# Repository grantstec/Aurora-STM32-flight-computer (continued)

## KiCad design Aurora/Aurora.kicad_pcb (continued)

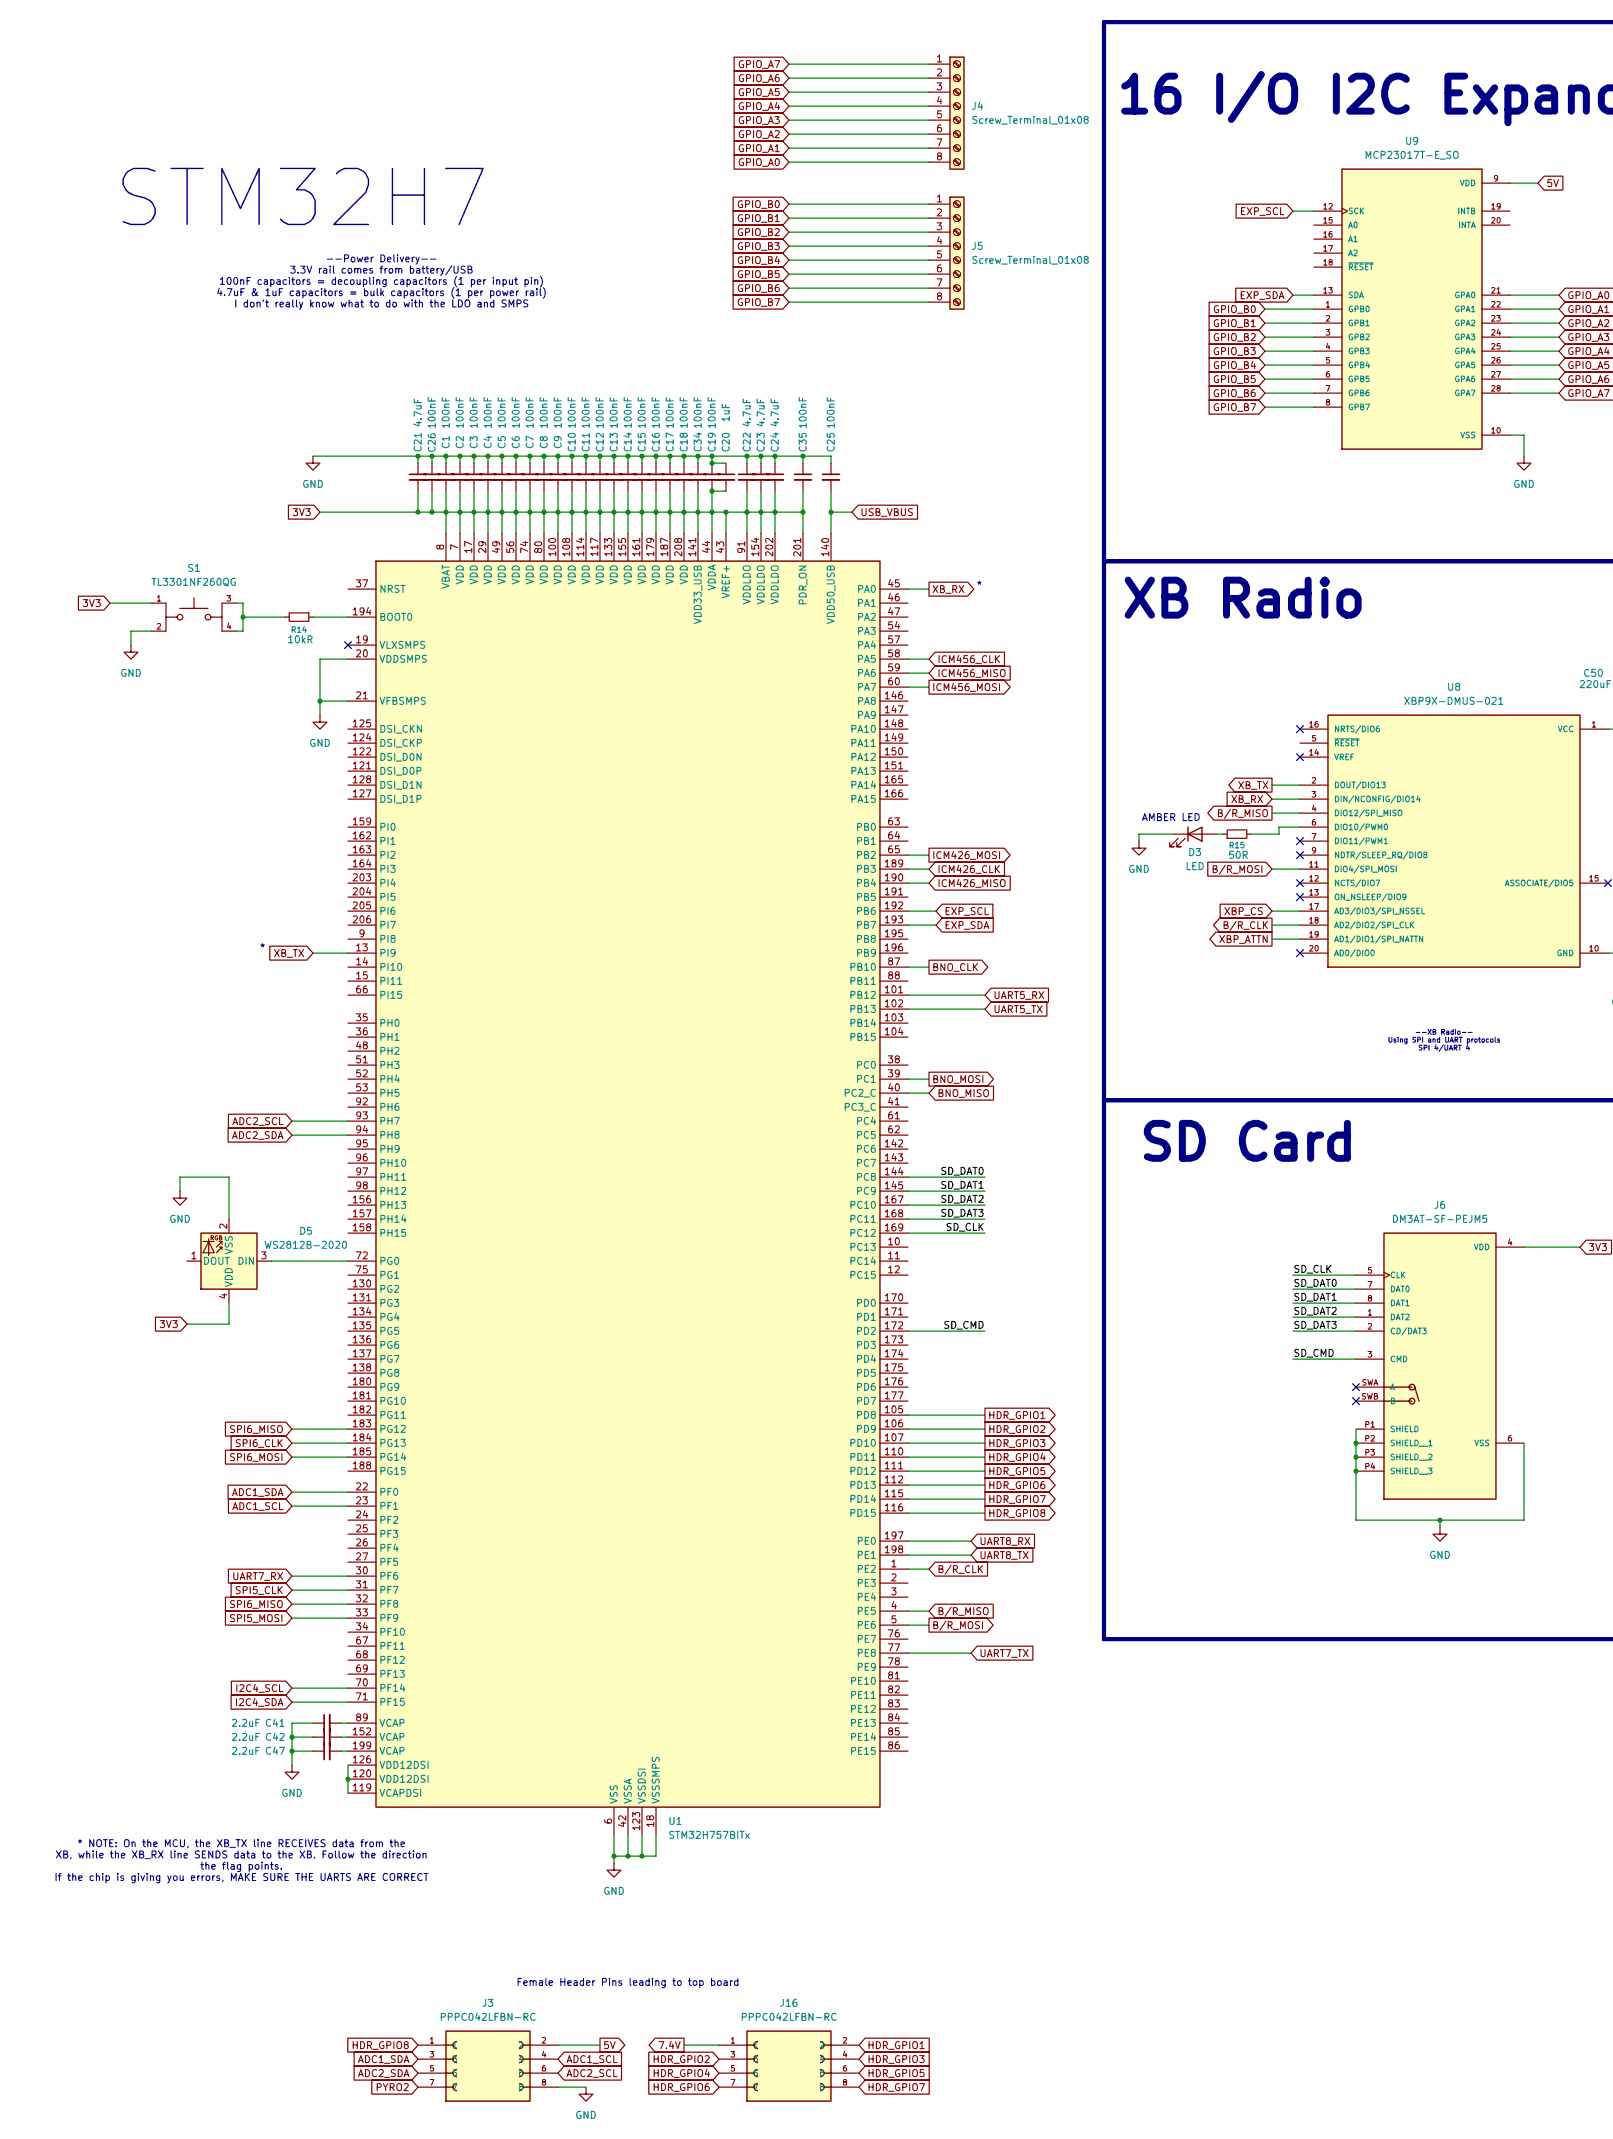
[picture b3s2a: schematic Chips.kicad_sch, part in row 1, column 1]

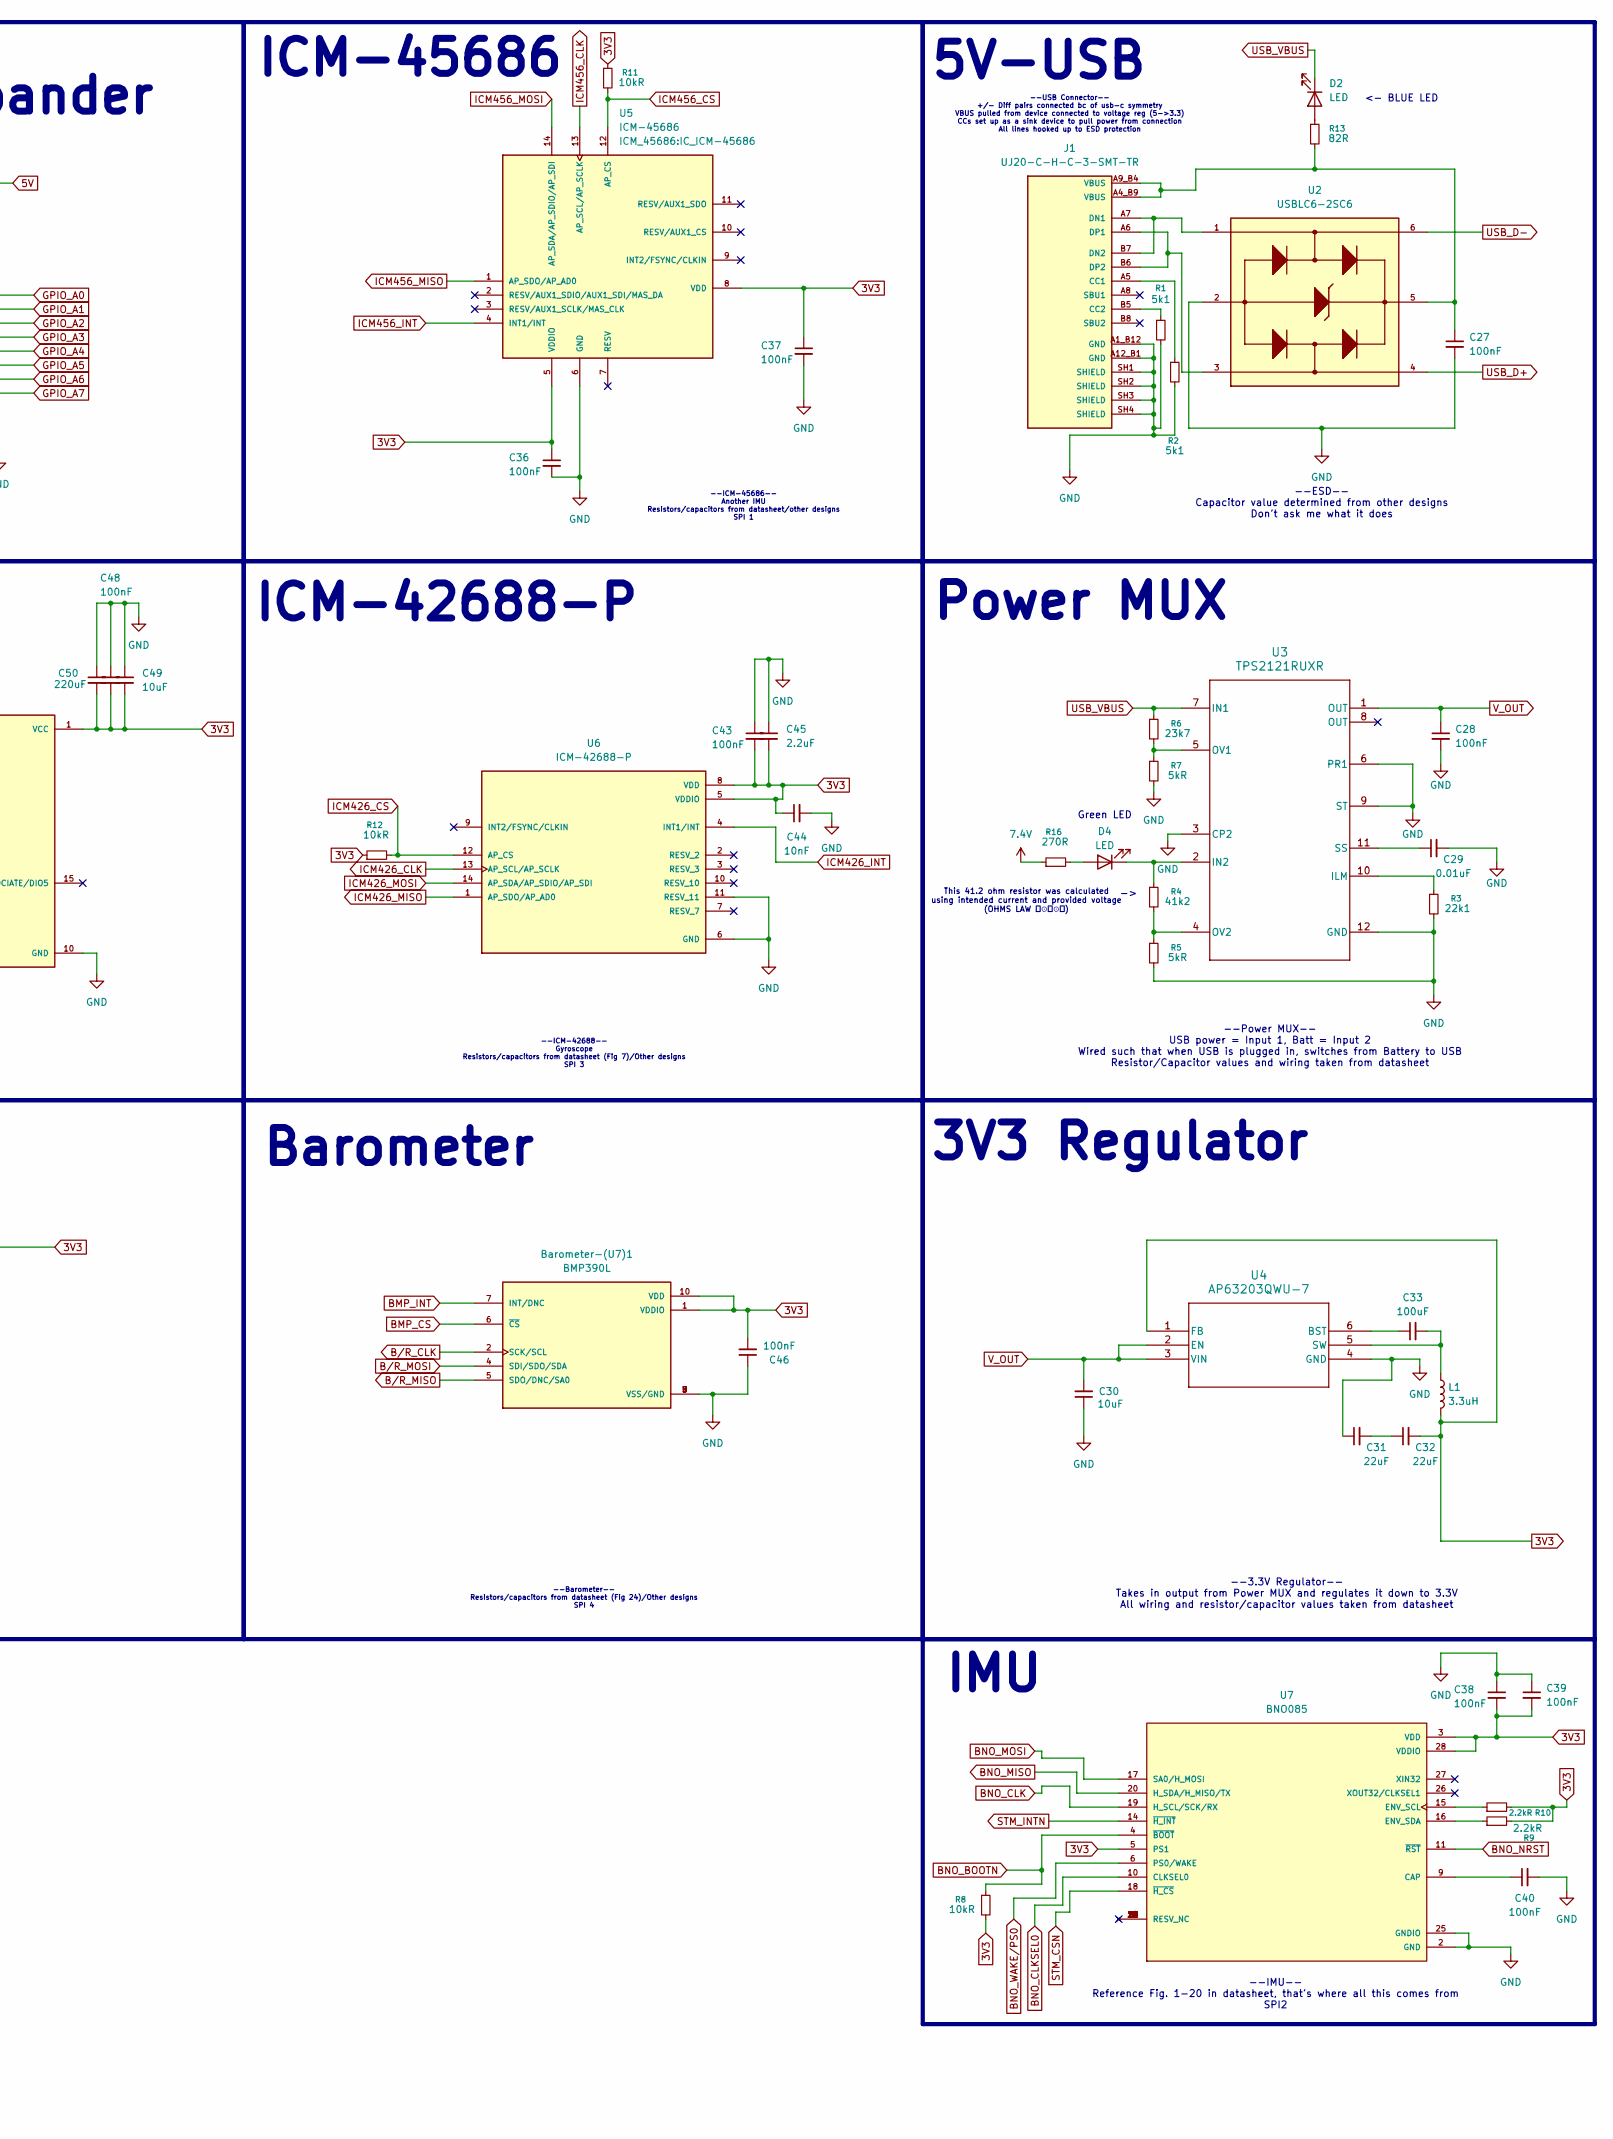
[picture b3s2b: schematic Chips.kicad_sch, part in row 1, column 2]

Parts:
Barometer-(U7)1: BMP390L; XDCR_BMP390L; PARTREV 1.7
C1, C2, C3, C4, C5, C6, C7, C8, C9, C10, C11, C12, C13, C14, C15, C16, C17, C18, C19, C25, C26, C27, C28, C34, C35, C36, C37, C38, C39, C40, C43, C46, C48: 100nF; C_1206_3216Metric
C20: 1uF; C_1206_3216Metric
C21, C22, C23, C24: 4.7uF; C_1206_3216Metric
C29: 0.01uF; C_1206_3216Metric
C30, C49: 10uF; C_1206_3216Metric
C31, C32: 22uF; C_1206_3216Metric
C33: 100uF; C_1206_3216Metric
C41, C42, C45, C47: 2.2uF; C_1206_3216Metric
C44: 10nF; C_1206_3216Metric
C50: 220uF; C_1206_3216Metric
D2, D3, D4: LED; LED_Cree-PLCC4_5x5mm_CW
D5: WS2812B-2020; LED_WS2812B-2020_PLCC4_2.0x2.0mm
J1: UJ20-C-H-C-3-SMT-TR; CUI_UJ20-C-H-C-3-SMT-TR; PARTREV 1.0
J3, J16: PPPC042LFBN-RC; SULLINS_PPPC042LFBN-RC; PARTREV L
J4, J5: Screw_Terminal_01x08; CONN_1715789_PXC
J6: DM3AT-SF-PEJM5; HRS_DM3AT-SF-PEJM5; PARTREV 20200913
L1: 3.3uH; L_1206_3216Metric
R1, R2: 5k1; R_1206_3216Metric
R3: 22k1; R_1206_3216Metric
R4: 41k2; R_1206_3216Metric
R5, R7: 5kR; R_1206_3216Metric
R6: 23k7; R_1206_3216Metric
R8, R11, R12, R14: 10kR; R_1206_3216Metric
R9, R10: 2.2kR; R_1206_3216Metric
R13: 82R; R_1206_3216Metric
R15: 50R; R_1206_3216Metric
R16: 270R; R_1206_3216Metric
S1: TL3301NF260QG; SW_TL3301NF260QG; PARTREV E
U1: STM32H757BITx; LQFP-208_28x28mm_P0.5mm
U2: USBLC6-2SC6; SOT95P280X145-6N
U3: TPS2121RUXR; RUX0012A
U4: AP63203QWU-7; TSOT26_DIO
U5: ICM-45686; IC_ICM-45686; PARTREV 0.2
U6: ICM-42688-P; PQFN50P300X250X97-14N; PARTREV 1.2
U7: BNO085; IC_BNO085; PARTREV v1.17
U8: XBP9X-DMUS-021; DIP2200W51P200L3294H279Q20P; DigiKey_Part_Number 602-1916-ND
U9: MCP23017T-E_SO; SOIC127P1030X265-28N

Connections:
3V3: Barometer-(U7)1.1 (VDDIO), Barometer-(U7)1.10 (VDD), C1.2, C2.2, C3.2, C4.2, C5.2, C6.2, C7.2, C8.2, C9.2, C10.2, C11.2, C12.2, C13.2, C14.2, C15.2, C16.2, C17.2, C18.2, C19.2, C20.2, C21.2, C22.2, C23.2, C24.2, C26.2, C32.2, C34.2, C35.2, C36.1, C37.1, C38.2, C39.2, C43.2, C44.1, C45.2, C46.2, C48.2, C49.2, C50.2, D5.4 (VDD), J6.4 (VDD), L1.2, R8.2, R9.2, R10.2, R11.1, R12.1, S1.1, U1.7 (VDD), U1.8 (VBAT), U1.17 (VDD), U1.29 (VDD), U1.43 (VREF+), U1.44 (VDDA), U1.49 (VDD), U1.56 (VDD), U1.74 (VDD), U1.80 (VDD), U1.91 (VDDLDO), U1.100 (VDD), U1.108 (VDD), U1.114 (VDD), U1.117 (VDD), U1.133 (VDD), U1.141 (VDD33_USB), U1.154 (VDDLDO), U1.155 (VDD), U1.161 (VDD), U1.179 (VDD), U1.187 (VDD), U1.201 (PDR_ON), U1.202 (VDDLDO), U1.208 (VDD), U4.1 (FB), U5.5 (VDDIO), U5.8 (VDD), U6.5 (VDDIO), U6.8 (VDD), U7.3 (VDD), U7.5 (PS1), U7.28 (VDDIO), U8.1 (VCC)
5V: J3.2, U9.9 (VDD); also elsewhere on the board
7.4V: J16.1, R16.1; also elsewhere on the board
/Chips/SD_CLK: J6.5 (CLK), U1.169 (PC12)
/Chips/SD_CMD: J6.3 (CMD), U1.172 (PD2)
/Chips/SD_DAT0: J6.7 (DAT0), U1.144 (PC8)
/Chips/SD_DAT1: J6.8 (DAT1), U1.145 (PC9)
/Chips/SD_DAT2: J6.1 (DAT2), U1.167 (PC10)
/Chips/SD_DAT3: J6.2 (CD/DAT3), U1.168 (PC11)
ADC1_SCL: J3.4, U1.23 (PF1); also elsewhere on the board
ADC1_SDA: J3.3, U1.22 (PF0); also elsewhere on the board
ADC2_SCL: J3.6, U1.93 (PH7); also elsewhere on the board
ADC2_SDA: J3.5, U1.94 (PH8); also elsewhere on the board
BMP_CS: Barometer-(U7)1.6 (~CS)
BMP_INT: Barometer-(U7)1.7 (INT/DNC)
BNO_BOOTN: R8.1, U7.4 (~BOOT)
BNO_CLK: U1.87 (PB10), U7.19 (H_SCL/SCK/RX)
BNO_CLKSEL0: U7.10 (CLKSEL0)
BNO_MISO: U1.40 (PC2_C), U7.20 (H_SDA/H_MISO/TX)
BNO_MOSI: U1.39 (PC1), U7.17 (SA0/H_MOSI)
BNO_NRST: U7.11 (~RST)
BNO_WAKE/PS0: U7.6 (PS0/WAKE)
B/R_CLK: Barometer-(U7)1.2 (SCK/SCL), U1.1 (PE2), U8.18 (AD2/DIO2/SPI_CLK)
B/R_MISO: Barometer-(U7)1.5 (SDO/DNC/SA0), U1.4 (PE5), U8.4 (DIO12/SPI_MISO)
B/R_MOSI: Barometer-(U7)1.4 (SDI/SDO/SDA), U1.5 (PE6), U8.11 (DIO4/SPI_MOSI)
EXP_SCL: U1.192 (PB6), U9.12 (SCK)
EXP_SDA: U1.193 (PB7), U9.13 (SDA)
GND: Barometer-(U7)1.3 (VSS/GND), Barometer-(U7)1.8 (VSS/GND), Barometer-(U7)1.9 (VSS/GND), C1.1, C2.1, C3.1, C4.1, C5.1, C6.1, C7.1, C8.1, C9.1, C10.1, C11.1, C12.1, C13.1, C14.1, C15.1, C16.1, C17.1, C18.1, C19.1, C20.1, C21.1, C22.1, C23.1, C24.1, C25.1, C26.1, C27.2, C28.2, C29.2, C30.1, C31.1, C34.1, C35.1, C36.2, C37.2, C38.1, C39.1, C40.2, C41.1, C42.1, C43.1, C44.2, C45.1, C46.1, C47.1, C48.1, C49.1, C50.1, D3.1 (K), D5.2 (VSS), J1.A1_B12 (GND), J1.A12_B1 (GND), J1.SH1 (SHIELD), J1.SH2 (SHIELD), J1.SH3 (SHIELD), J1.SH4 (SHIELD), J3.8, J6.6 (VSS), J6.P1 (SHIELD), J6.P2 (SHIELD__1), J6.P3 (SHIELD__2), J6.P4 (SHIELD__3), R1.2, R2.2, R3.2, R5.2, R7.2, S1.2, U1.6 (VSS), U1.16 (VSS), U1.18 (VSSSMPS), U1.20 (VDDSMPS), U1.21 (VFBSMPS), U1.28 (VSS), U1.42 (VSSA), U1.50 (VSS), U1.55 (VSS), U1.73 (VSS), U1.79 (VSS), U1.90 (VSS), U1.99 (VSS), U1.109 (VSS), U1.113 (VSS), U1.118 (VSS), U1.123 (VSSDSI), U1.129 (VSSDSI), U1.132 (VSS), U1.139 (VSS), U1.153 (VSS), U1.160 (VSS), U1.178 (VSS), U1.186 (VSS), U1.200 (VSS), U1.207 (VSS), U2.2, U3.3 (CP2), U3.6 (PR1), U3.9 (ST), U3.12 (GND), U4.4 (GND), U5.6 (GND), U6.6 (GND), U6.11 (RESV_11), U7.2 (GND), U7.25 (GNDIO), U8.10 (GND), U9.10 (VSS); also elsewhere on the board
GPIO_A0: J4.8, U9.21 (GPA0); also elsewhere on the board
GPIO_A1: J4.7, U9.22 (GPA1); also elsewhere on the board
GPIO_A2: J4.6, U9.23 (GPA2); also elsewhere on the board
GPIO_A3: J4.5, U9.24 (GPA3); also elsewhere on the board
GPIO_A4: J4.4, U9.25 (GPA4); also elsewhere on the board
GPIO_A5: J4.3, U9.26 (GPA5); also elsewhere on the board
GPIO_A6: J4.2, U9.27 (GPA6); also elsewhere on the board
GPIO_A7: J4.1, U9.28 (GPA7); also elsewhere on the board
GPIO_B0: J5.1, U9.1 (GPB0); also elsewhere on the board
GPIO_B1: J5.2, U9.2 (GPB1); also elsewhere on the board
GPIO_B2: J5.3, U9.3 (GPB2); also elsewhere on the board
GPIO_B3: J5.4, U9.4 (GPB3); also elsewhere on the board
GPIO_B4: J5.5, U9.5 (GPB4); also elsewhere on the board
GPIO_B5: J5.6, U9.6 (GPB5); also elsewhere on the board
GPIO_B6: J5.7, U9.7 (GPB6); also elsewhere on the board
GPIO_B7: J5.8, U9.8 (GPB7); also elsewhere on the board
HDR_GPIO1: J16.2, U1.105 (PD8); also elsewhere on the board
HDR_GPIO2: J16.3, U1.106 (PD9); also elsewhere on the board
HDR_GPIO3: J16.4, U1.107 (PD10); also elsewhere on the board
HDR_GPIO4: J16.5, U1.110 (PD11); also elsewhere on the board
HDR_GPIO5: J16.6, U1.111 (PD12); also elsewhere on the board
HDR_GPIO6: J16.7, U1.112 (PD13); also elsewhere on the board
HDR_GPIO7: J16.8, U1.115 (PD14); also elsewhere on the board
HDR_GPIO8: J3.1, U1.116 (PD15); also elsewhere on the board
I2C4_SCL: U1.70 (PF14); also elsewhere on the board
I2C4_SDA: U1.71 (PF15); also elsewhere on the board
ICM426_CLK: U1.189 (PB3), U6.13 (AP_SCL/AP_SCLK)
ICM426_CS: R12.2, U6.12 (AP_CS)
ICM426_INT: U6.4 (INT1/INT)
ICM426_MISO: U1.190 (PB4), U6.1 (AP_SDO/AP_AD0)
ICM426_MOSI: U1.65 (PB2), U6.14 (AP_SDA/AP_SDIO/AP_SDI)
ICM456_CLK: U1.58 (PA5), U5.13 (AP_SCL/AP_SCLK)
ICM456_CS: R11.2, U5.12 (AP_CS)
ICM456_INT: U5.4 (INT1/INT)
ICM456_MISO: U1.59 (PA6), U5.1 (AP_SDO/AP_AD0)
ICM456_MOSI: U1.60 (PA7), U5.14 (AP_SDA/AP_SDIO/AP_SDI)
unnamed: C27.1, J1.A4_B9 (VBUS), J1.A9_B4 (VBUS), R13.2, U2.5
unnamed: C31.2, C32.1
unnamed: C41.2, U1.89 (VCAP)
unnamed: C42.2, U1.152 (VCAP)
unnamed: C47.2, U1.199 (VCAP)
unnamed: D2.2 (A), R13.1
unnamed: D3.2 (A), R15.1
unnamed: D4.2 (A), R16.2
unnamed: D4.1 (K), R4.1, U3.2 (IN2)
unnamed: D5.3 (DIN), U1.72 (PG0)
unnamed: J1.A5 (CC1), R2.1
unnamed: J1.B5 (CC2), R1.1
unnamed: J1.A7 (DN1), J1.B7 (DN2), U2.1
unnamed: J1.A6 (DP1), J1.B6 (DP2), U2.3
unnamed: R14.2, S1.3, S1.4
unnamed: R14.1, U1.194 (BOOT0)
unnamed: U1.119 (VCAPDSI), U1.120 (VDD12DSI), U1.126 (VDD12DSI)
unnamed: R3.1, U3.10 (ILM)
unnamed: R6.2, R7.1, U3.5 (OV1)
unnamed: R4.2, R5.1, U3.4 (OV2)
unnamed: C29.1, U3.11 (SS)
unnamed: C33.1, U4.6 (BST)
unnamed: C33.2, L1.1, U4.5 (SW)
unnamed: C40.1, U7.9 (CAP)
unnamed: R10.1, U7.15 (ENV_SCL)
unnamed: R9.1, U7.16 (ENV_SDA)
unnamed: R15.2, U8.6 (DIO10/PWM0)
PYRO2: J3.7; also elsewhere on the board
SPI5_CLK: U1.31 (PF7); also elsewhere on the board
SPI5_MOSI: U1.33 (PF9); also elsewhere on the board
SPI6_CLK: U1.184 (PG13); also elsewhere on the board
SPI6_MISO: U1.32 (PF8), U1.183 (PG12); also elsewhere on the board
SPI6_MOSI: U1.185 (PG14); also elsewhere on the board
STM_CSN: U7.18 (~H_CS)
STM_INTN: U7.14 (~H_INT)
UART5_RX: U1.101 (PB12); also elsewhere on the board
UART5_TX: U1.102 (PB13); also elsewhere on the board
UART7_RX: U1.30 (PF6); also elsewhere on the board
UART7_TX: U1.77 (PE8); also elsewhere on the board
UART8_RX: U1.197 (PE0); also elsewhere on the board
UART8_TX: U1.198 (PE1); also elsewhere on the board
USB_D+: U2.4
USB_D-: U2.6
USB_VBUS: C25.2, D2.1 (K), R6.1, U1.140 (VDD50_USB), U3.7 (IN1)
V_OUT: C28.1, C30.2, U3.1 (OUT), U4.2 (EN), U4.3 (VIN)
XBP_ATTN: U8.19 (AD1/DIO1/SPI_NATTN)
XBP_CS: U8.17 (AD3/DIO3/SPI_NSSEL)
XB_RX: U1.45 (PA0), U8.3 (DIN/NCONFIG/DIO14)
XB_TX: U1.13 (PI9), U8.2 (DOUT/DIO13)

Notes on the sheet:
XB Radio
--XB Radio-- Using SPI and UART protocols SPI 4/UART 4
--Power MUX-- USB power = Input 1, Batt = Input 2 Wired such that when USB is plugged in, switches from Battery to USB Resistor/Capacitor values and wiring taken from datasheet
ICM-42688-P
Barometer
--Barometer-- Resistors/capacitors from datasheet (Fig 24)/Other designs SPI 4
--Power Delivery-- 3.3V rail comes from battery/USB 100nF capacitors = decoupling capacitors (1 per input pin) 4.7uF & 1uF capacitors = bulk capacitors (1 per power rail) I don't really know what to do with the LDO and SMPS
<- BLUE LED
--IMU-- Reference Fig. 1-20 in datasheet, that's where all this comes from SPI2
* NOTE: On the MCU, the XB_TX line RECEIVES data from the XB, while the XB_RX line SENDS data to the XB. Follow the direction the flag points. If the chip is giving you errors, MAKE SURE THE UARTS ARE CORRECT
Power MUX
--ESD-- Capacitor value determined from other designs Don't ask me what it does
Female Header Pins leading to top board
--ICM-42688-- Gyroscope Resistors/capacitors from datasheet (Fig 7)/Other designs SPI 3
--USB Connector-- +/- Diff pairs connected bc of usb-c symmetry VBUS pulled from device connected to voltage reg (5->3.3) CCs set up as a sink device to pull power from connection All lines hooked up to ESD protection
This 41.2 ohm resistor was calculated using intended current and provided voltage (OHMS LAW （⊙ｏ⊙）)
IMU
AMBER LED
Green LED
--3.3V Regulator-- Takes in output from Power MUX and regulates it down to 3.3V All wiring and resistor/capacitor values taken from datasheet
ICM-45686
STM32H7
3V3 Regulator
5V-USB
16 I/O I2C Expander
--ICM-45686-- Another IMU Resistors/capacitors from datasheet/other designs SPI 1
SD Card

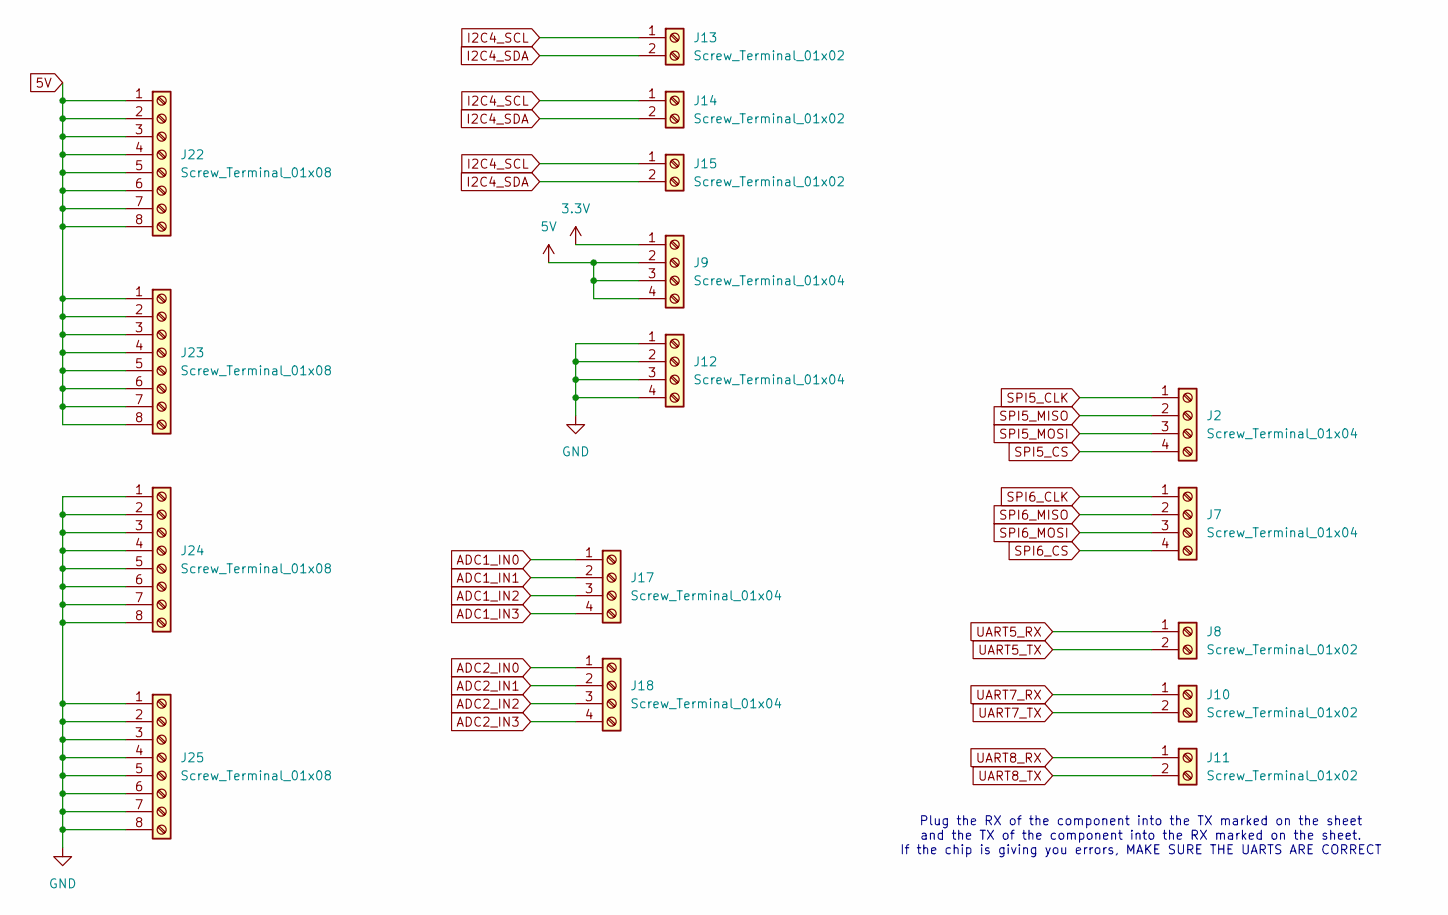
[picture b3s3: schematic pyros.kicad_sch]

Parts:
J2, J7, J9, J12, J17, J18: Screw_Terminal_01x04; CONN_1715747_PXC
J8, J10, J11, J13, J14, J15: Screw_Terminal_01x02; CONN_1729128_PXC
J22, J23, J24, J25: Screw_Terminal_01x08; CONN_1715789_PXC

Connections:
3.3V: J9.1
5V: J9.2, J9.3, J9.4; also elsewhere on the board
ADC1_IN0: J17.1; also elsewhere on the board
ADC1_IN1: J17.2; also elsewhere on the board
ADC1_IN2: J17.3; also elsewhere on the board
ADC1_IN3: J17.4; also elsewhere on the board
ADC2_IN0: J18.1; also elsewhere on the board
ADC2_IN1: J18.2; also elsewhere on the board
ADC2_IN2: J18.3; also elsewhere on the board
ADC2_IN3: J18.4; also elsewhere on the board
GND: J12.1, J12.2, J12.3, J12.4, J24.1, J24.2, J24.3, J24.4, J24.5, J24.6, J24.7, J24.8, J25.1, J25.2, J25.3, J25.4, J25.5, J25.6, J25.7, J25.8; also elsewhere on the board
I2C4_SCL: J13.1, J14.1, J15.1; also elsewhere on the board
I2C4_SDA: J13.2, J14.2, J15.2; also elsewhere on the board
unnamed: J22.1, J22.2, J22.3, J22.4, J22.5, J22.6, J22.7, J22.8, J23.1, J23.2, J23.3, J23.4, J23.5, J23.6, J23.7, J23.8
SPI5_CLK: J2.1; also elsewhere on the board
SPI5_CS: J2.4
SPI5_MISO: J2.2
SPI5_MOSI: J2.3; also elsewhere on the board
SPI6_CLK: J7.1; also elsewhere on the board
SPI6_CS: J7.4
SPI6_MISO: J7.2; also elsewhere on the board
SPI6_MOSI: J7.3; also elsewhere on the board
UART5_RX: J8.1; also elsewhere on the board
UART5_TX: J8.2; also elsewhere on the board
UART7_RX: J10.1; also elsewhere on the board
UART7_TX: J10.2; also elsewhere on the board
UART8_RX: J11.1; also elsewhere on the board
UART8_TX: J11.2; also elsewhere on the board

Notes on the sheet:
Plug the RX of the component into the TX marked on the sheet and the TX of the component into the RX marked on the sheet. If the chip is giving you errors, MAKE SURE THE UARTS ARE CORRECT

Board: 2 copper layers, 109 parts (0 on the bottom side), 108 nets, no tracks yet.

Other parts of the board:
J4#2, J5#2: Screw_Terminal_01x08; CONN_1715789_PXC

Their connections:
GPIO_A0: J4#2.8; also elsewhere on the board
GPIO_A1: J4#2.7; also elsewhere on the board
GPIO_A2: J4#2.6; also elsewhere on the board
GPIO_A3: J4#2.5; also elsewhere on the board
GPIO_A4: J4#2.4; also elsewhere on the board
GPIO_A5: J4#2.3; also elsewhere on the board
GPIO_A6: J4#2.2; also elsewhere on the board
GPIO_A7: J4#2.1; also elsewhere on the board
GPIO_B0: J5#2.1; also elsewhere on the board
GPIO_B1: J5#2.2; also elsewhere on the board
GPIO_B2: J5#2.3; also elsewhere on the board
GPIO_B3: J5#2.4; also elsewhere on the board
GPIO_B4: J5#2.5; also elsewhere on the board
GPIO_B5: J5#2.6; also elsewhere on the board
GPIO_B6: J5#2.7; also elsewhere on the board
GPIO_B7: J5#2.8; also elsewhere on the board

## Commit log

2025-08-23 Enhance README with TO-DO and resources
    Added a TO-DO list and resources section to the README.
2025-08-23 Fix formatting of TO-DO and Resources sections
2025-08-23 first
2025-09-04 test
2025-09-04 hooked VDD pins to power, includes decoupling and bulk capacitors
2025-09-08 finished power pins
2025-09-08 fixed capacitors
2025-09-08 hooked up USB receptacle, added ESD protection
2025-09-10 updates to USB connection
2025-09-13 Voltage regulator, some comments
2025-09-13 added 7.4->5v regulator for battery
2025-09-13 power multiplexer
2025-09-13 ICM and other sensors
2025-09-13 3.3v regulator
2025-09-13 changed position of components on schm
2025-09-13 Add KiCad auto merge workflow
2025-09-13 Implement 3-way KiCad-aware auto-merge script
    This script implements a 3-way auto-merge for KiCad files, handling conflicts based on specified rules for different object types and merging strategies.
2025-09-13 Add 3-way auto-merge script for KiCad files
    This script provides a 3-way auto-merge functionality for KiCad files, handling conflicts based on specified rules for different object types.
2025-09-13 Add KiCad auto-merge GitHub Actions workflow
2025-09-13 ci: trigger auto-merge
2025-09-13 Add workflow_dispatch trigger to auto merge
2025-09-13 Add workflow_dispatch to KiCad auto merge workflow
2025-09-15 worked on figuring out VDD12DSI pins and VDDSMPS pins, hopefully this is correct
2025-09-16 changes to capacitors, LDO, SMPS stuff
2025-09-16 Revert "merging conflicts"
    This reverts commit 3d8ae35df3231aee76086947d4fef95e6f82343e, reversing
    changes made to c2fa33c742d47faaac57159af77864f609f31e02.
2025-09-18 began wiring up sensors
2025-09-23 did some work on gyroscope, wired up IMU
2025-09-23 began wiring ICM-45686 and BNO085 to chip
2025-09-24 wired up ICM-45686, ICM-42688, and Barometer to STM
2025-10-14 SD Card wired up
2025-10-16 Hooked up XB radio, began breaking out the rest of the SPI and UART pins
2025-11-17 lots of changes; sensors, LEDs, screw terminal blocks
2025-11-18 reorganization
2025-11-18 3rd ADC
2025-11-18 Boot0 and NRST pins
2025-12-01 All CS pins include 10k pullups on SPI buses
2025-12-02 some changes to the reset and boot pins, wip
2026-01-05 new baro
2026-01-05 PU resistor on CS for baro
2026-01-09 added new regulator chain + rationale
2026-01-14 regulators mount up
2026-01-22 bom updates (purchase links, prices, etc) and switching imu because out of stock
2026-01-22 undo imu switch grant got scammed
2026-01-26 added pyros, voltage booster
2026-01-29 working though GPIOs/CSs, Xref with cubeMX
2026-01-30 continued updating gpios and interrupt pins
2026-02-03 BNO/baro pins, pullups added to all active low pins on Baro
2026-02-03 pullup on BNO CS
2026-02-05 done with debug header pins
2026-02-06 added breakouts for xb and stlink
2026-02-12 fixed header pins, XB on UART
2026-02-12 NOW the xb is on UART
2026-02-17 changes to net labelling
2026-02-25 fixed schematic issues, started organizing components in PCB
2026-03-06 layout and changed screw term size
2026-03-18 changing a lot of stuff, like components and footprints
